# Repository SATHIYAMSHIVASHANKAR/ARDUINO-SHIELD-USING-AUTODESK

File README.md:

# ARDUINO-SHIELD-USING-AUTODESK
DEVEOPING AN ARDUNIO SHIELD USING IC MAX7219 USING AUTODESK - EAGLE
***
step 1: In Autodesk Eagle, create a new project under the project sector. Name the file as Arduino Shield. Now under Arduino Shield create a Schematic file.
***
step 2: Allocate nessasary grid lines value in the grid section such that the editor page comes with the sutable grid lines
***
step 3: Using Add components tool, take the required parts and place it in the schematic with refernce to the circuit diagram. 
***
step 4: In order to reduce the complexcity in wire connection, introduce bus connection using Bus tool.
***
step 5: In Bus connection, it is mandatory to give Alias name and the Specification. Through this we can connet the Net (wire) conection at ease.
***
step 6: Now connect the components in the schematic using Net tool. 
***
step 7: Refer the data sheet to allocate the values to the components by using Value tool.
***
step 8 Its is mandatory to create a Net class for the ciruit made in Schematic. Create two net classes, name them as Power and MAX7219 NET and add the nessasary values to the Member section. Enter the respective terms to Default and Power sections.
***
step 9: To frame the entire circuit, select a Frame of your choice in Add components tool, place it around the circuit in schematic.
***
step 10: Now create a board, Delete the board lines which defaultly appears when creating the board. This is done because Arduino itself is a board, such that the components can be moved into the board (Arduino).
***
step 11: Move the components into the board and route the components using Air Routeing tool. The routing will be a bit complicated such that use both top as well as bottom layer for routing. Usage of Via tool is Mandatory to skip the part of intersection with wire.
***
step 12: Select Polygon tool and extend its strech to the entire board except Real Time Clock (rtc) and the Crystal component. Name it as Ground. Now by appling Ratsnest tool, the polygon (ground) gets activated.
***
step 13: Change the layer to Bottom. extend the Polygon all over the board, and to acitvate it apply Ratsnets tool as followed in step 12.
***
step 14: To give the name to board use Name tool. Enter the appropriate name and place it on the board with the Name Layer activated.
***
step 15: If required drill four holes in corner using Hole tool. By accessing Manufacturing tool we will get to know about the completed Audrino Board.
***

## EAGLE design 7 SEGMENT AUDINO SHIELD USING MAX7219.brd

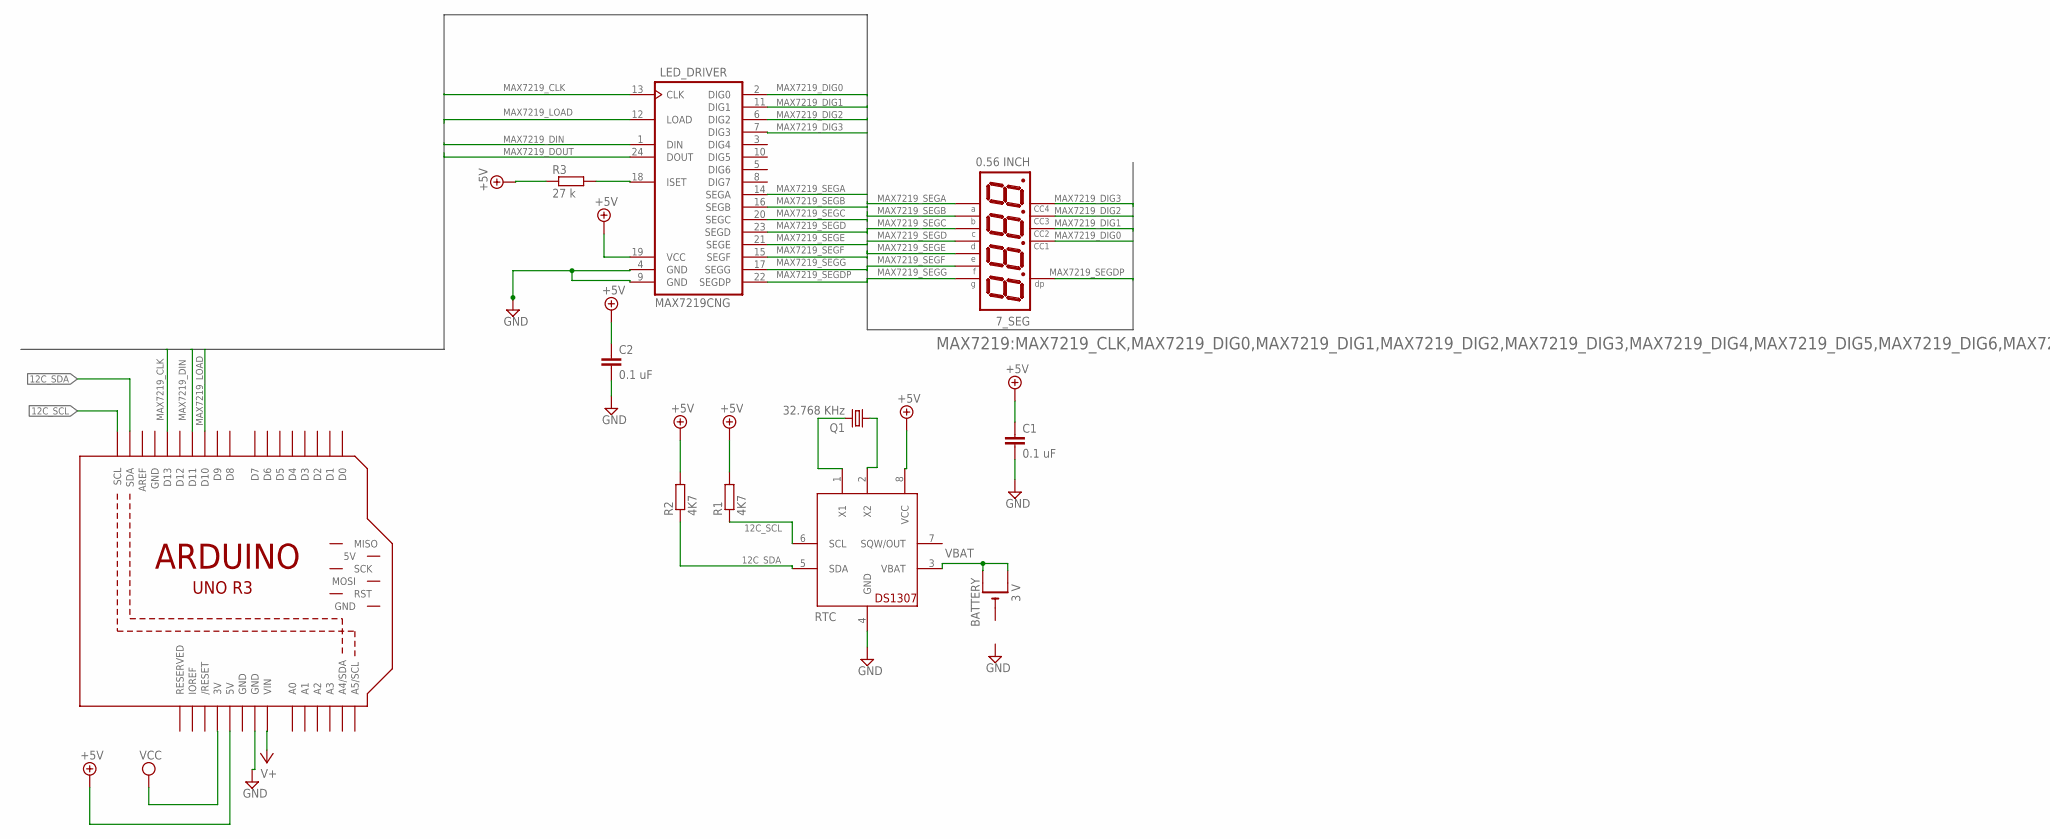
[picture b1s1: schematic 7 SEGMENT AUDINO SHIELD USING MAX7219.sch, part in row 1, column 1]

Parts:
7_SEG: 0.56 INCH; NFD-5641
BATTERY: 3 V; CR1220-SMD
C1: 0.1 uF; C050-030X075
C2: 0.1 uF; C1206
LED_DRIVER: MAX7219CNG; DIL24-3
M1: ARDUINO_R3_ICSP; ARDUINOR3_ICSP
Q1: 32.768 KHz; TC26H
R1, R2: 4K7; R1206
R3: 27 k; R1206
RTC: DS1307; DIL08

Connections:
12C_SCL: M1.SCL, R1.1, RTC.6 (SCL)
12C_SDA: M1.SDA, R2.1, RTC.5 (SDA)
+5V: C1.1, C2.1, LED_DRIVER.19 (VCC), M1.5V, R1.2, R2.2, R3.1, RTC.8 (VCC)
GND: C1.2, C2.2, LED_DRIVER.4 (GND), LED_DRIVER.9 (GND), M1.GND, M1.GND@1 (GND), M1.GND@3 (GND), RTC.4 (GND)
MAX7219_CLK: LED_DRIVER.13 (CLK), M1.D13
MAX7219_DIG0: 7_SEG.P$12, LED_DRIVER.2 (DIG0)
MAX7219_DIG1: 7_SEG.P$9, LED_DRIVER.11 (DIG1)
MAX7219_DIG2: 7_SEG.P$8, LED_DRIVER.6 (DIG2)
MAX7219_DIG3: 7_SEG.P$6, LED_DRIVER.7 (DIG3)
MAX7219_DIN: LED_DRIVER.1 (DIN), M1.D11
MAX7219_DOUT: LED_DRIVER.24 (DOUT)
MAX7219_LOAD: LED_DRIVER.12 (LOAD), M1.D10
MAX7219_SEGA: 7_SEG.P$11, LED_DRIVER.14 (SEGA)
MAX7219_SEGB: 7_SEG.P$7, LED_DRIVER.16 (SEGB)
MAX7219_SEGC: 7_SEG.P$4, LED_DRIVER.20 (SEGC)
MAX7219_SEGD: 7_SEG.P$2, LED_DRIVER.23 (SEGD)
MAX7219_SEGDP: 7_SEG.P$3, LED_DRIVER.22 (SEGDP)
MAX7219_SEGE: 7_SEG.P$1, LED_DRIVER.21 (SEGE)
MAX7219_SEGF: 7_SEG.P$10, LED_DRIVER.15 (SEGF)
MAX7219_SEGG: 7_SEG.P$5, LED_DRIVER.17 (SEGG)
unnamed: LED_DRIVER.18 (ISET), R3.2
unnamed: Q1.2, RTC.1 (X1)
unnamed: Q1.1, RTC.2 (X2)
V+: M1.VIN
VBAT: BATTERY.+$1 (+), BATTERY.+$2 (+1), RTC.3 (VBAT)
VCC: M1.3V

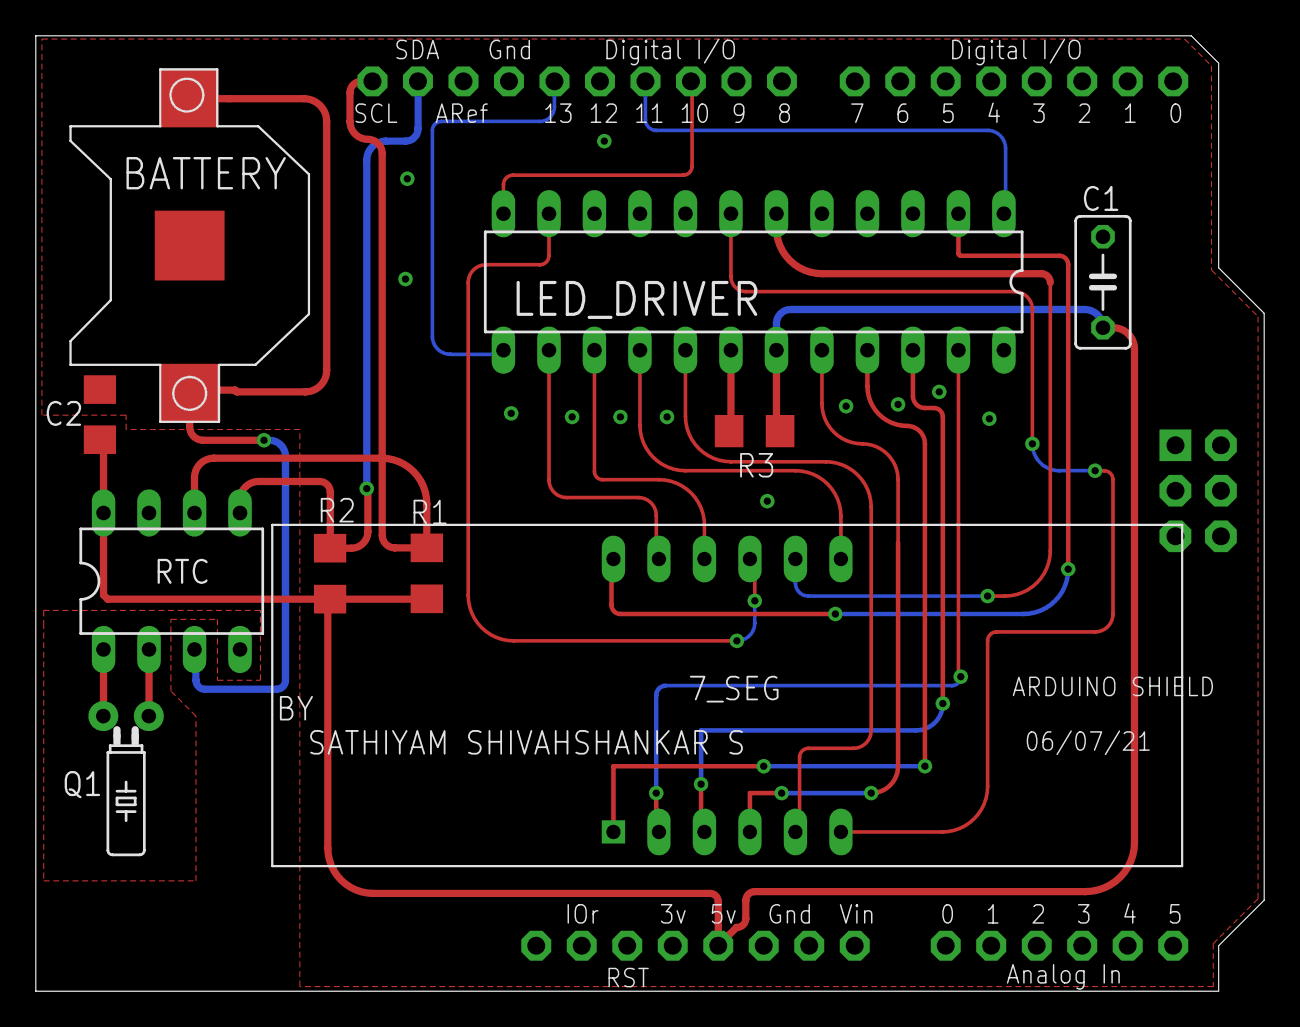
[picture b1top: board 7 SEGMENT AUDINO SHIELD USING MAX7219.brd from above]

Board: 2 copper layers, 68.6 x 53.3 mm, 11 parts (0 on the bottom side), 23 nets.
